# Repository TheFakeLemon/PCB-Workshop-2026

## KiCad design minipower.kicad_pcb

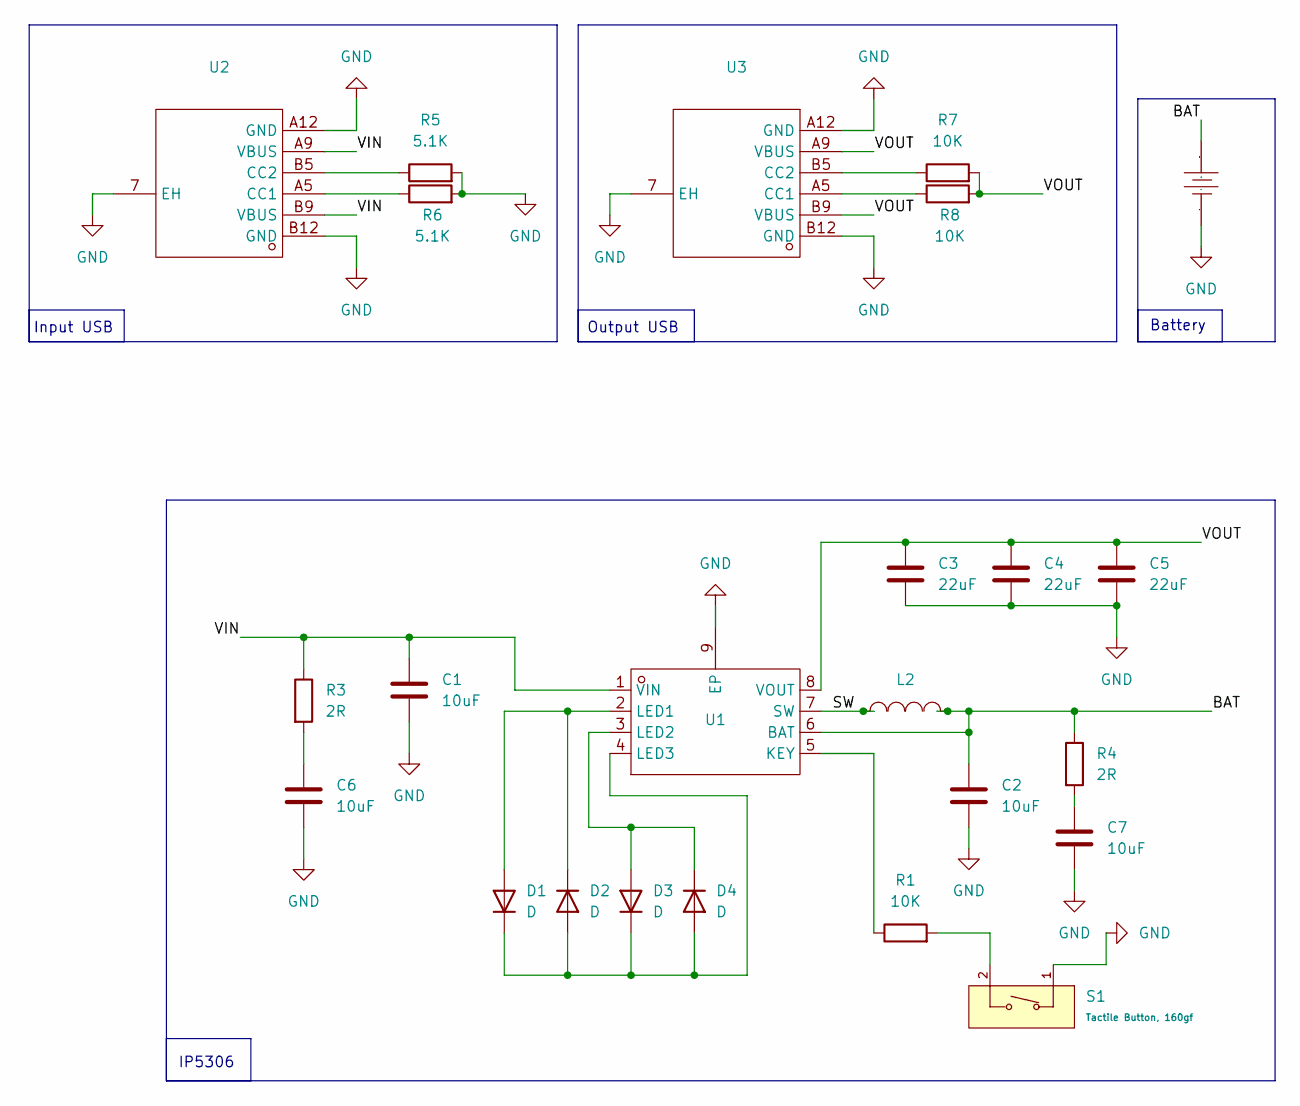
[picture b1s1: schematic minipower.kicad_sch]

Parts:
C1, C2, C6, C7: 10uF; C_0603_1608Metric
C3, C4, C5: 22uF; C_1206_3216Metric
D1, D2, D3, D4: D; LED_0603_1608Metric
L2: 1uH; IND-SMD_L7.1-W6.5-P5.60; Manufacturer Part SMNR4020-1UH; LCSC Part Name 1uH ±20% 4.78A
R1, R7, R8: 10K; R_0402_1005Metric
R3, R4: 2R; R_0603_1608Metric
R5, R6: 5.1K; R_0402_1005Metric
S1: Tactile Button, 160gf; SW_TS-1088-AR02016; Voltage Rating (Dc) 12V; Part TS-1088-AR02016; LCSC C720477
U1: ESOP-8_L4.9-W3.9-P1.27-LS6.0-BL-EP; Manufacturer Part IP5306; LCSC Part Name 集成2.1A充电器和2.1A放电器的全集成移动电源系统级芯片
U2, U3: TYPE-C-SMD_TYPE-C-6P; Manufacturer Part USB-TYPE-C-009; LCSC Part Name Type-C 母 卧贴
U6: BAT-TH_BH-21700-A5BJ001; Manufacturer Part BH-21700-A5BJ001; LCSC Part Name BH-21700-A5BJ001

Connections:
/BAT: C2.1, L2.2, R4.1, U1.6 (BAT), U6.1
/SW: L2.1, U1.7 (SW)
/VIN: C1.1, R3.1, U1.1 (VIN), U2.A9 (VBUS), U2.B9 (VBUS)
/VOUT: C3.1, C4.1, C5.1, R7.2, R8.2, U1.8 (VOUT), U3.A9 (VBUS), U3.B9 (VBUS)
GND: C1.2, C2.2, C3.2, C4.2, C5.2, C6.2, C7.2, R5.2, R6.2, S1.1 (A), U1.9 (EP), U2.7 (EH), U2.A12 (GND), U2.B12 (GND), U3.7 (EH), U3.A12 (GND), U3.B12 (GND), U6.2
unnamed: C6.1, R3.2
unnamed: C7.1, R4.2
unnamed: D1.2 (A), D2.1 (K), U1.2 (LED1)
unnamed: D1.1 (K), D2.2 (A), D3.1 (K), D4.2 (A), U1.4 (LED3)
unnamed: D3.2 (A), D4.1 (K), U1.3 (LED2)
unnamed: R1.2, S1.2 (B)
unnamed: R1.1, U1.5 (KEY)
unnamed: R6.1, U2.A5 (CC1)
unnamed: R5.1, U2.B5 (CC2)
unnamed: R8.1, U3.A5 (CC1)
unnamed: R7.1, U3.B5 (CC2)

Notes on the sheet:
IP5306
Battery
Input USB
Output USB

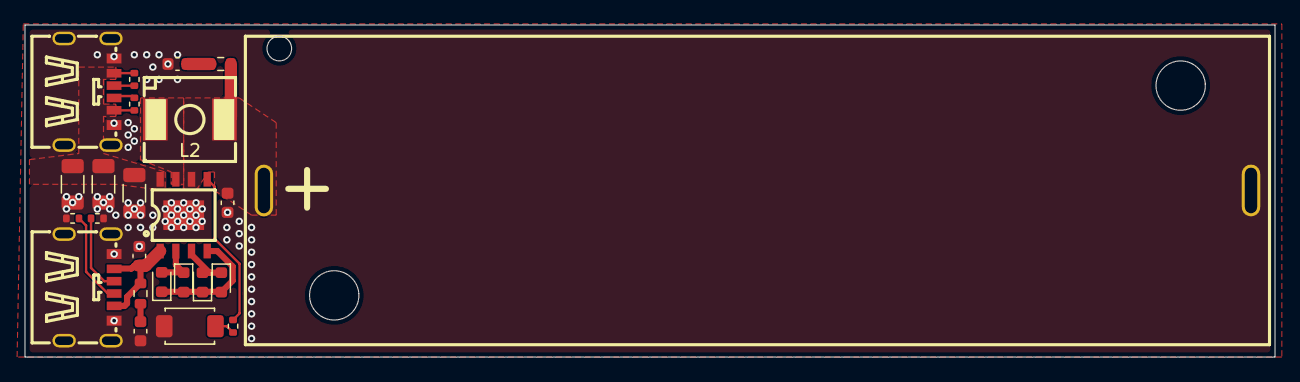
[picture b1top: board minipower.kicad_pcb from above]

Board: 2 copper layers, 101.3 x 26.9 mm, 24 parts (0 on the bottom side), 16 nets.

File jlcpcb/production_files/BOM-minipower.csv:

Comment,Designator,Footprint,LCSC,Quantity
10K,"R1,R7,R8",R_0402_1005Metric,C25744,3
10uF,"C1,C2,C6,C7",C_0603_1608Metric,C19702,4
1uH,L2,IND-SMD_L7.1-W6.5-P5.60,C87572,1
22uF,"C3,C4,C5",C_1206_3216Metric,C12891,3
2R,"R3,R4",R_0603_1608Metric,C22977,2
5.1K,"R5,R6",R_0402_1005Metric,C25905,2
D,"D1,D2,D3,D4",LED_0603_1608Metric,C2286,4
"Tactile Button, 160gf",S1,SW_TS-1088-AR02016,C720477,1
~,U1,ESOP-8_L4.9-W3.9-P1.27-LS6.0-BL-EP,C181692,1
~,U6,BAT-TH_BH-21700-A5BJ001,C20606809,1
~,"U2,U3",TYPE-C-SMD_TYPE-C-6P,C2927029,2
Burden_Bear_40,REF**,Burden_Bear_40,,1

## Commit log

2026-02-28 version3
    initial commit; previously not uploaded to github
2026-02-28 Added custom footprint and library tables for participants
2026-02-28 tidying up
2026-03-09 add graphic
2026-03-09 cleaning up
    some changes to graphics, had mental breakdown over how to source battery holders
2026-03-09 backups updated
    s
2026-03-24 neatened schematic
2026-04-16 export
2026-04-21 gitignore update
2026-04-21 remove backups
